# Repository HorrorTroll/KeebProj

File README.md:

# Keyboards

This repository is warehouse of my keyboard architecture.

## Paws60

### About Paws60

The Paws60 is 63 key (60%) keyboard. It is based on [Bakeneko60](https://github.com/kkatano/bakeneko-60). Thank you so much kkatano.😊

[Firmware](https://github.com/qmk/qmk_firmware/tree/master/keyboards/horrortroll/paws60)  
[Hardware data](https://github.com/HorrorTroll/Keeb_Project/tree/default/paws60)

## Sakura50

### About Sakura50

The Sakura50 is 56 keys (50%) keyboard.

[Firmware]()  
[Hardware data](https://github.com/HorrorTroll/Keeb_Project/tree/default/sakura50)

## Keeb65 (Abandon)

### About Keeb65

The Keeb65 is 67 key (65%) keyboard. For many reason, it become abandon project.

[Firmware]()  
[Hardware data](https://github.com/HorrorTroll/Keeb_Project/tree/default/keeb65)

## ToxicDog69

### About ToxicDog69

The ToxicDog69 is 69 keys Multi-layout (65%) keyboard.

[Firmware]()  
[Hardware data](https://github.com/HorrorTroll/Keeb_Project/tree/default/toxicdog69)

## LazuliPad

### About LazuliPad

The LazuliPad is a Numpad Multi-layout keyboard.

[Firmware]()  
[Hardware data](https://github.com/HorrorTroll/Keeb_Project/tree/default/lazulipad)

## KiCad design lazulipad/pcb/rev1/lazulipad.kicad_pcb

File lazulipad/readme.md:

# LazuliPad PCB
 A Numpad Multi-Layout Hotswap Type-C PCB, designed in KiCAD 6.99. The name was based on Lazuli Lapis stones.

**This board not have any prototyped yet!**

Renders (KiCAD):
- **Revision 1**:

## Features
**Revision 1**:
- Uses the AT32F403ACGT7 MCU (new), with 1MB of internal flash and 16MB of external flash
- Uses Kailh Hotswap Sockets
- Added anti-shearing to the hotswap sockets
- Holes of hotswap socket holes are plated, you can still solder in a switch, should a hotswap socket ever shear off for whatever reason
- Multi-layout (see below)
- USB-C connector
- Physical Reset and BOOT0 button for getting into bootloader if [bootmagic](https://github.com/qmk/qmk_firmware/blob/master/docs/feature_bootmagic.md) isn't available. Acessible both of them under PCB.
- SWD header for debugging
- ESD chip (PRTR5V0U2X) to prevent damage from electrostatic discharge
- Polyfuse to prevent overcurrent
- Stabilizer only supported Plate Mount, prevent 90-degree hotswap socket.
- Supported LCD module (ST7789 / 135 X 240).
- Supported 1 Rotary Encoder (EC11)
- Bonus: Curved traces and teardrops

## Firmware
**Coming soon!**

## Multi-Layout Support

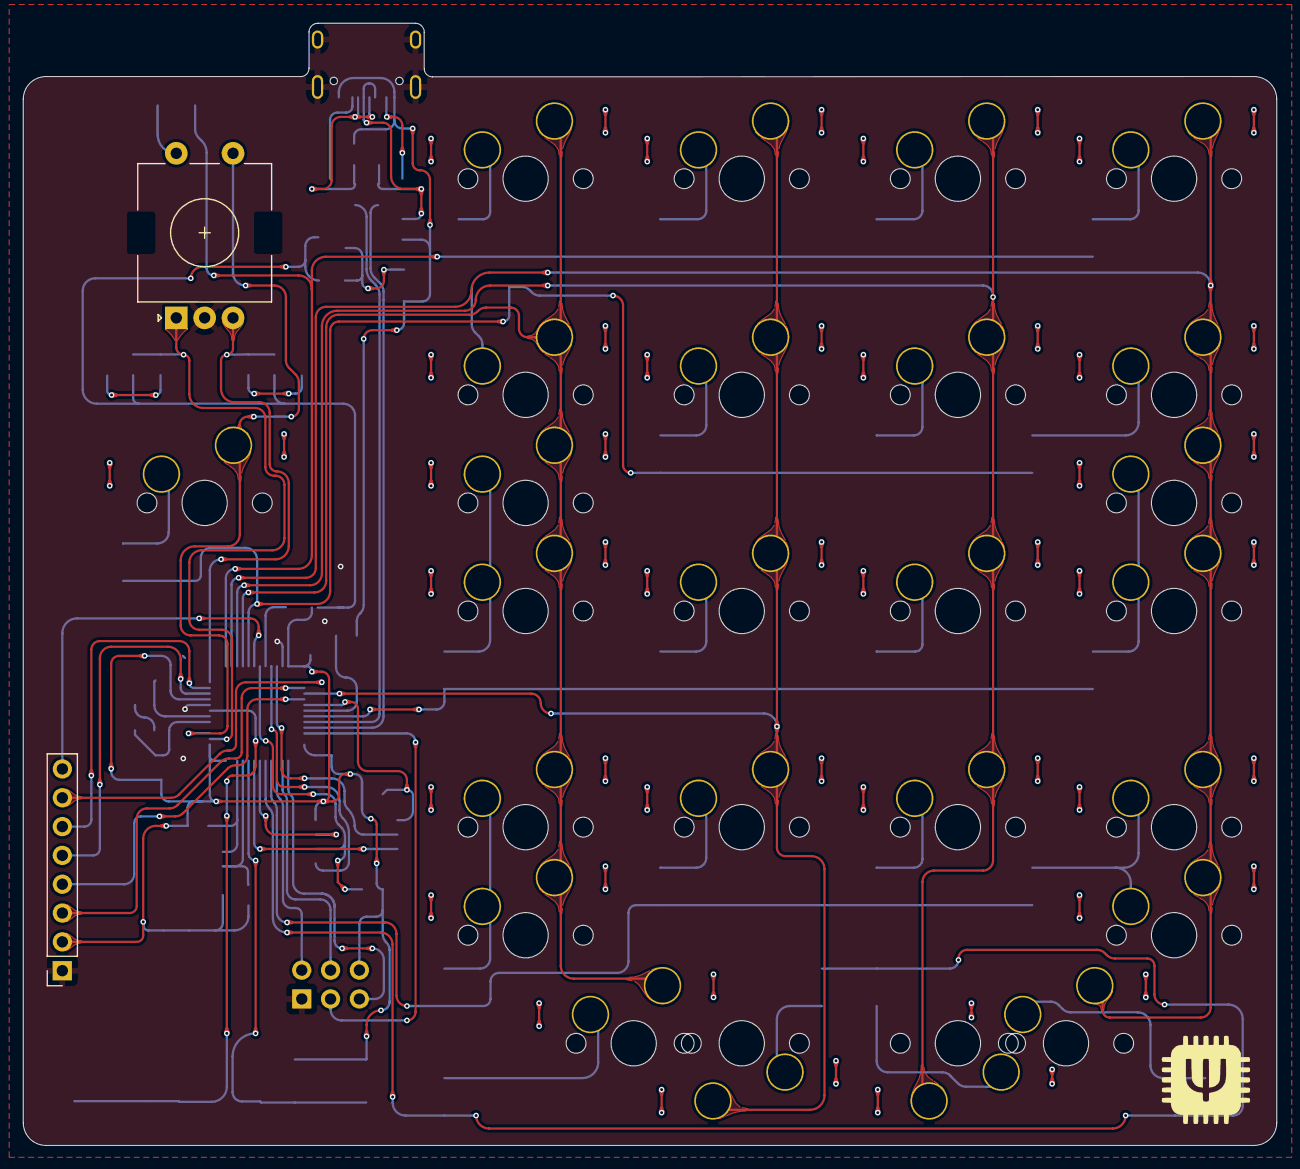
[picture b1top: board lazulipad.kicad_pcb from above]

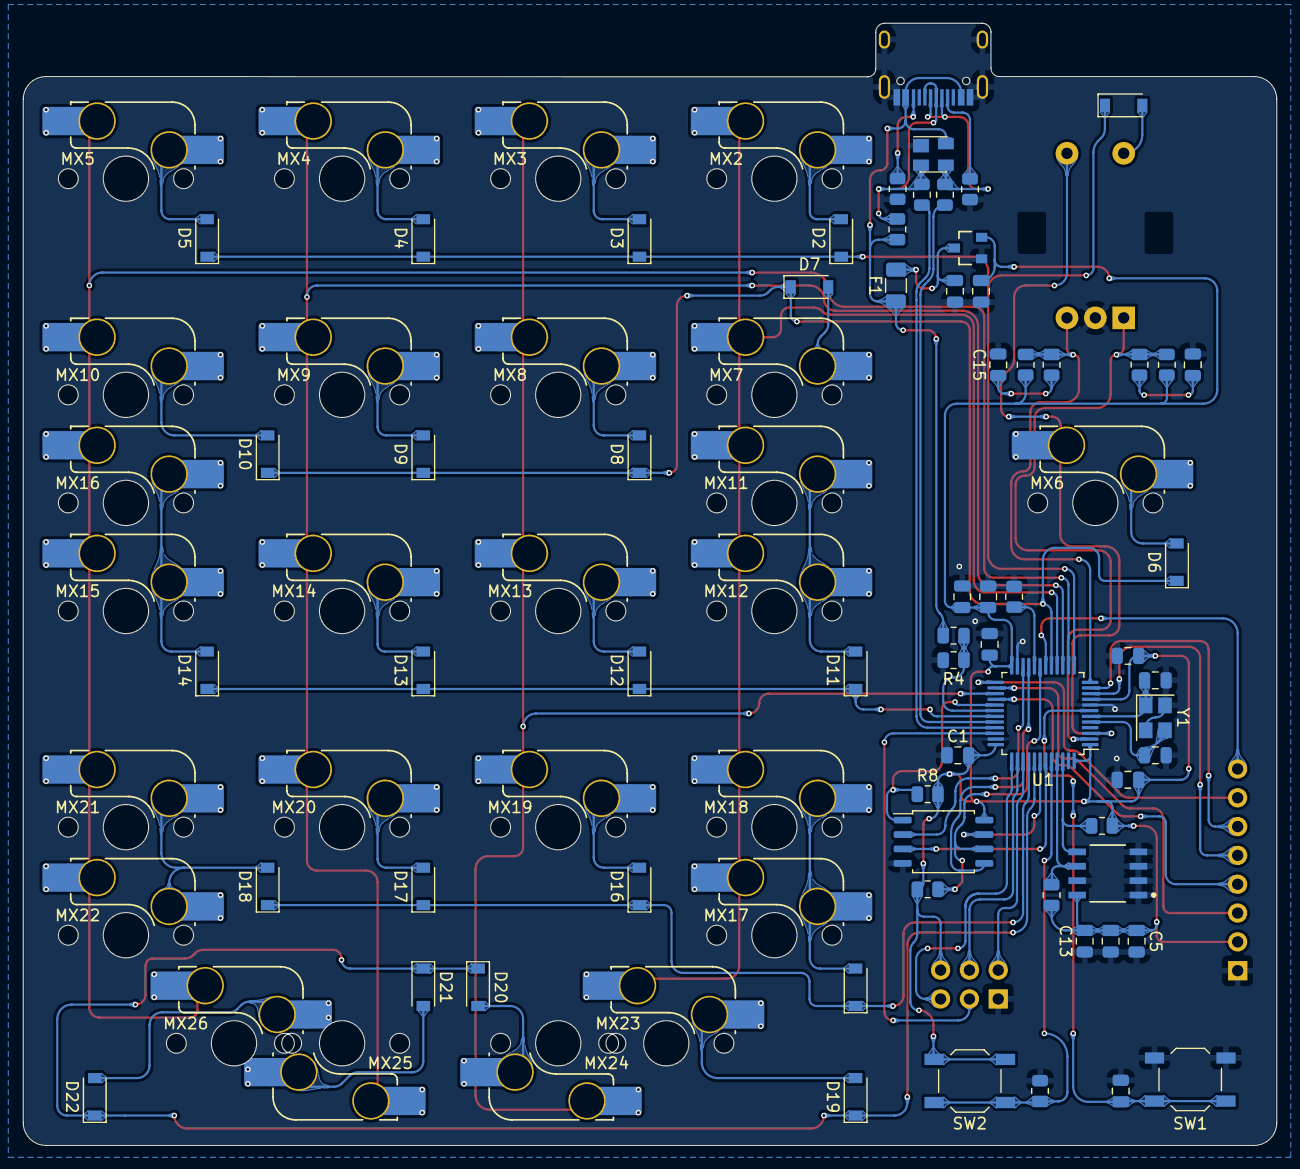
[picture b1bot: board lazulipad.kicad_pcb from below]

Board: 2 copper layers, 110.5 x 98.9 mm, 93 parts (90 on the bottom side), 70 nets.

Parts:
C1, C2, C5, C7, C13, C14, C15, C16: 100n; C_0805_2012Metric
C3: 10n; C_0805_2012Metric
C4, C11, C12: 1u; C_0805_2012Metric
C6, C8: 4.7u; C_0805_2012Metric
C9, C10: 22p; C_0805_2012Metric
D1, D2, D3, D4, D5, D6, D7, D8, D9, D10, D11, D12, D13, D14, D15, D16, D17, D18, D19, D20, D21, D22: 1N4148W; D_SOD-123
ESD1: PRTR5V0U2X; SOT-143
F1: 500mA; Fuse_1206_3216Metric
J1: ARM-JTAG-6; Reset_Pretty_nosilk
LCD1: LCD-ST7789-1.14in; PinSocket_1x08_P2.54mm_Vertical
MX1: Enc; RotaryEncoder_EC11
MX2, MX3, MX4, MX5, MX6, MX7, MX8, MX9, MX10, MX12, MX13, MX14, MX15, MX18, MX19, MX20, MX21, MX24, MX25: 1u; SW_MX_HS_1u
MX11, MX16, MX17, MX22: 2u; SW_MX_HS_2u_vertical
MX23, MX26: 2u; SW_MX_HS_2u
R1, R2, R5, R6, R8: 10K; R_0805_2012Metric
R3: 100k; R_0805_2012Metric
R4: 200k; R_0805_2012Metric
R7: 1K; R_0805_2012Metric
R9, R10: 5.1k; R_0805_2012Metric
R11, R12, R13, R14: 10k; R_0805_2012Metric
R15, R16: 22R; R_0805_2012Metric
R17: 1.5K; R_0805_2012Metric
RG1: XC6206P332MR; Torex-XC6206P332MR
SW1: RESET; SW_SPST_TL3342
SW2: BOOT0; SW_SPST_TL3342
U1: STM32F103CBTx; LQFP-48_7x7mm_P0.5mm
U2: W25Q128JVS; SOIC-8_5.23x5.23mm_P1.27mm
U3: AT24C512C-SSHD-T; Microchip-C04-057-SN-0-E-MFG
USB1: HRO-TYPE-C-31-M-12
Y1: 8Mhz; Crystal_SMD_3225-4Pin_3.2x2.5mm

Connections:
+3V3: C1.2, C2.2, C3.2, C4.2, C5.1, C6.1, C7.1, C8.1, C12.1, C13.2, J1.1 (VCC), LCD1.2, R5.2, R6.2, R7.2, R8.2, R11.1, R12.1, RG1.2 (VOUT), SW2.2, U1.1 (VBAT), U1.9 (VDDA), U1.24 (VDD), U1.36 (VDD), U1.48 (VDD), U2.8 (VCC), U3.8 (VCC)
+5V: C11.1, F1.2, RG1.3 (VIN)
/DM: ESD1.3 (I/O2), R16.2, USB1.5 (DN2), USB1.7 (DN1)
/DP: ESD1.2 (I/O1), R15.2, R17.2, USB1.6 (DP1), USB1.8 (DP2)
/VBUS_DETECT: R3.2, R4.1, U1.30 (PA9)
BLK: LCD1.8, U1.18 (PB0)
BOOT0: R1.1, SW2.1, U1.44 (BOOT0)
BOOT1: R2.1, U1.20 (PB2)
CS: LCD1.7, U1.25 (PB12)
Col0: MX1.S1, MX6.2 (B), U1.3 (PC14)
Col1: MX2.2 (B), MX7.2 (B), MX11.2 (B), MX12.2 (B), MX17.2 (B), MX18.2 (B), MX23.2 (B), U1.16 (PA6)
Col2: MX3.2 (B), MX8.2 (B), MX13.2 (B), MX19.2 (B), MX24.2 (B), U1.27 (PB14)
Col3: MX4.2 (B), MX9.2 (B), MX14.2 (B), MX20.2 (B), MX25.2 (B), U1.15 (PA5)
Col4: MX5.2 (B), MX10.2 (B), MX15.2 (B), MX16.2 (B), MX21.2 (B), MX22.2 (B), MX26.2 (B), U1.14 (PA4)
D+: R15.1, U1.33 (PA12)
D-: R16.1, U1.32 (PA11)
DC: LCD1.6, U1.11 (PA1)
GND: C1.1, C2.1, C3.1, C4.1, C5.2, C6.2, C7.2, C8.2, C9.2, C10.2, C11.2, C12.2, C13.1, C14.2, C15.2, C16.1, ESD1.1 (GND), J1.6 (GND), LCD1.1, MX1.C, R1.2, R2.2, R4.2, R9.1, R10.2, RG1.1 (VSS), SW1.1, U1.8 (VSSA), U1.23 (VSS), U1.35 (VSS), U1.47 (VSS), U2.4 (GND), U3.1 (A0), U3.2 (A1), U3.3 (A2), U3.4 (GND), U3.7 (WP), USB1.1 (GND), USB1.12 (GND), USB1.13 (SHIELD), Y1.2, Y1.4
JTDI: J1.3 (JTDI), U1.38 (PA15)
JTDO: J1.5 (JTDO), U1.39 (PB3)
MOSI: LCD1.4, U1.28 (PB15)
NRST: C16.2, SW1.2, U1.7 (NRST)
unnamed: C14.1, R13.2
unnamed: C15.1, R14.2
unnamed: D1.2 (A), MX1.S2
unnamed: D2.2 (A), MX2.1 (A)
unnamed: D3.2 (A), MX3.1 (A)
unnamed: D4.2 (A), MX4.1 (A)
unnamed: D5.2 (A), MX5.1 (A)
unnamed: D6.2 (A), MX6.1 (A)
unnamed: D7.2 (A), MX7.1 (A)
unnamed: D8.2 (A), MX8.1 (A)
unnamed: D9.2 (A), MX9.1 (A)
unnamed: D10.2 (A), MX10.1 (A)
unnamed: D11.2 (A), MX11.1 (A), MX12.1 (A)
unnamed: D12.2 (A), MX13.1 (A)
unnamed: D13.2 (A), MX14.1 (A)
unnamed: D14.2 (A), MX15.1 (A), MX16.1 (A)
unnamed: D15.2 (A), MX17.1 (A), MX18.1 (A)
unnamed: D16.2 (A), MX19.1 (A)
unnamed: D17.2 (A), MX20.1 (A)
unnamed: D18.2 (A), MX21.1 (A), MX22.1 (A)
unnamed: D19.2 (A), MX23.1 (A)
unnamed: D20.2 (A), MX24.1 (A)
unnamed: D21.2 (A), MX25.1 (A)
unnamed: D22.2 (A), MX26.1 (A)
unnamed: R9.2, USB1.4 (CC1)
unnamed: R10.1, USB1.10 (CC2)
RESET: LCD1.5, U1.10 (PA0)
ROT0: MX1.A, R11.2, R13.1, U1.2 (PC13)
ROT1: MX1.B, R12.2, R14.1, U1.12 (PA2)
Row0: D1.1 (K), D2.1 (K), D3.1 (K), D4.1 (K), D5.1 (K), U1.13 (PA3)
Row1: D6.1 (K), D7.1 (K), D8.1 (K), D9.1 (K), D10.1 (K), U1.17 (PA7)
Row2: D11.1 (K), D12.1 (K), D13.1 (K), D14.1 (K), U1.31 (PA10)
Row3: D15.1 (K), D16.1 (K), D17.1 (K), D18.1 (K), U1.40 (PB4)
Row4: D19.1 (K), D20.1 (K), D21.1 (K), D22.1 (K), U1.41 (PB5)
SCK: LCD1.3, U1.26 (PB13)
SCL: R6.1, U1.45 (PB8), U3.6 (SCL)
SDA: R5.1, U1.46 (PB9), U3.5 (SDA)
SPIM_CS: R8.1, U1.29 (PA8), U2.1 (~CS)
SPIM_IO0: U1.21 (PB10), U2.5 (DI(IO0))
SPIM_IO1: U1.22 (PB11), U2.2 (DO(IO1))
SPIM_IO2: U1.43 (PB7), U2.3 (IO2)
SPIM_IO3: U1.42 (PB6), U2.7 (IO3)
SPIM_SCK: R7.1, U1.19 (PB1), U2.6 (CLK)
SWCLK-JTCK: J1.2 (SWCLK), U1.37 (PA14)
SWDIO-JTMS: J1.4 (SWDIO), U1.34 (PA13)
VBUS: ESD1.4 (VCC), F1.1, R3.1, R17.1, USB1.2 (VBUS), USB1.11 (VBUS)
XTAL1: C9.1, U1.5 (PD0), Y1.3
XTAL2: C10.1, U1.6 (PD1), Y1.1

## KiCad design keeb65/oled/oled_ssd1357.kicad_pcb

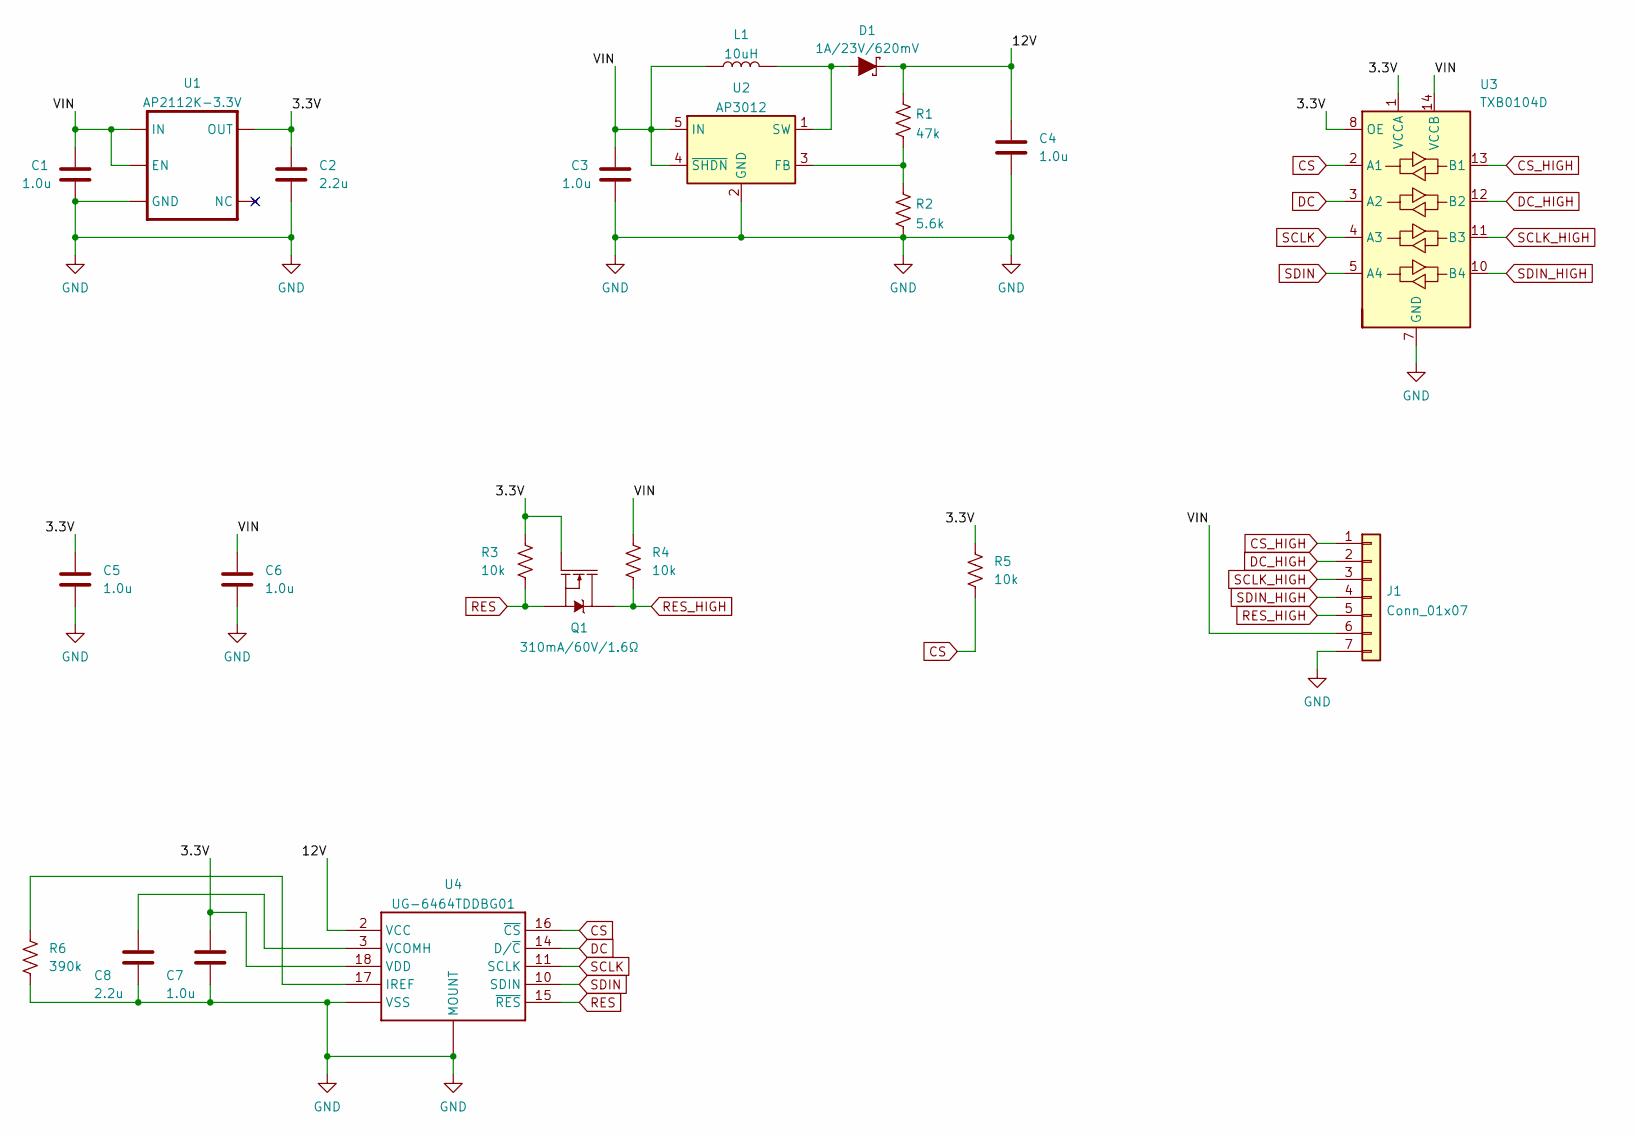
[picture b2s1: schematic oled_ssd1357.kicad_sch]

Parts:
C1, C3, C4, C5, C6, C7: 1.0u; C_0603_1608Metric
C2, C8: 2.2u; C_0603_1608Metric
D1: 1A/23V/620mV; SOD-323
J1: Conn_01x07; Molex_200528-0070_1x07-1MP_P1.00mm_Horizontal
L1: 10uH; CDRH124
Q1: 310mA/60V/1.6Ω; SOT65P210X110-3N
R1: 47k; R_0603_1608Metric
R2: 5.6k; R_0603_1608Metric
R3, R4, R5: 10k; R_0603_1608Metric
R6: 390k; R_0603_1608Metric
U1: AP2112K-3.3V; SOT-23-5
U2: AP3012; SOT-23-5
U3: TXB0104D; TXB0104
U4: UG-6464TDDBG01; AMPHENOL_10051922-2010ELF

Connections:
/3.3V: C2.1, C5.1, C7.1, Q1.1 (G), R3.1, R5.1, U1.5 (OUT), U3.1 (VCCA), U3.8 (OE), U4.18 (VDD)
/12V: C4.1, D1.C, R1.1, U4.2 (VCC)
/VIN: C1.1, C3.1, C6.1, J1.6, L1.P$1 (1), R4.1, U1.1 (IN), U1.3 (EN), U2.4 (~SHDN), U2.5 (IN), U3.14 (VCCB)
CS: R5.2, U3.2 (A1), U4.16 (~CS)
CS_HIGH: J1.1, U3.13 (B1)
DC: U3.3 (A2), U4.14 (D/~C)
DC_HIGH: J1.2, U3.12 (B2)
GND: C1.2, C2.2, C3.2, C4.2, C5.2, C6.2, C7.2, C8.2, J1.7, R2.2, R6.2, U1.2 (GND), U2.2 (GND), U3.7 (GND), U4.1 (VSS), U4.19 (VSS), U4.20 (VSS), U4.P$21 (MOUNT), U4.P$22 (MOUNT)
unnamed: C8.1, U4.3 (VCOMH)
unnamed: D1.A, L1.P$2 (2), U2.1 (SW)
unnamed: R1.2, R2.1, U2.3 (FB)
unnamed: R6.1, U4.17 (IREF)
RES: Q1.2 (S), R3.2, U4.15 (~RES)
RES_HIGH: J1.5, Q1.3 (D), R4.2
SCLK: U3.4 (A3), U4.11 (SCLK)
SCLK_HIGH: J1.3, U3.11 (B3)
SDIN: U3.5 (A4), U4.10 (SDIN)
SDIN_HIGH: J1.4, U3.10 (B4)

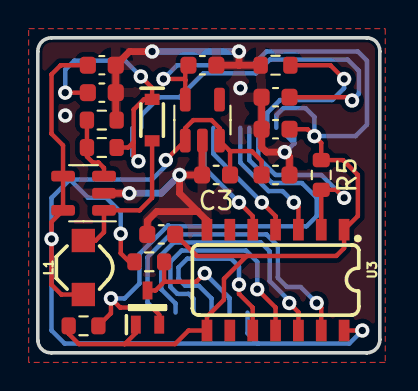
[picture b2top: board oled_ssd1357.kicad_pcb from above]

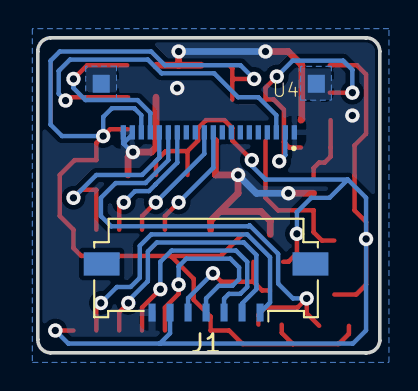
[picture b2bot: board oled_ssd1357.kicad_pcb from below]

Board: 2 copper layers, 19.0 x 17.5 mm, 22 parts (2 on the bottom side), 18 nets.

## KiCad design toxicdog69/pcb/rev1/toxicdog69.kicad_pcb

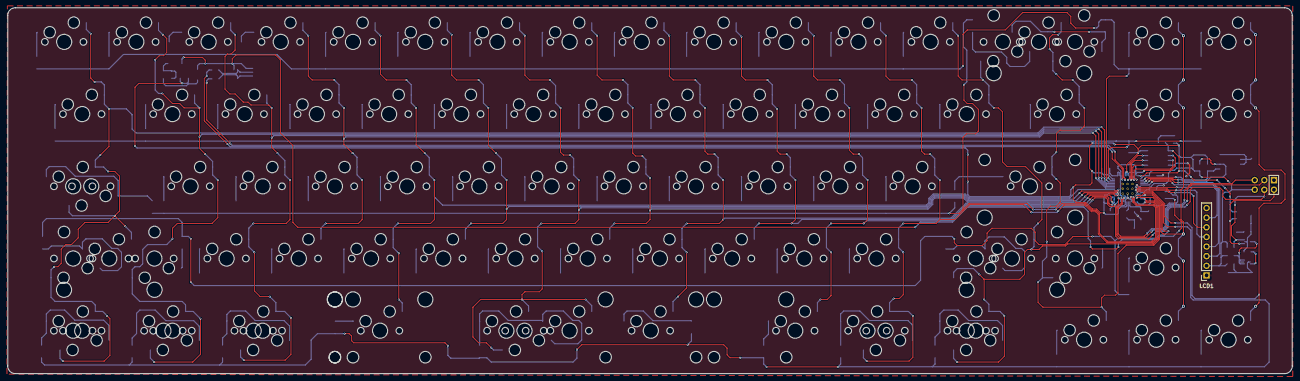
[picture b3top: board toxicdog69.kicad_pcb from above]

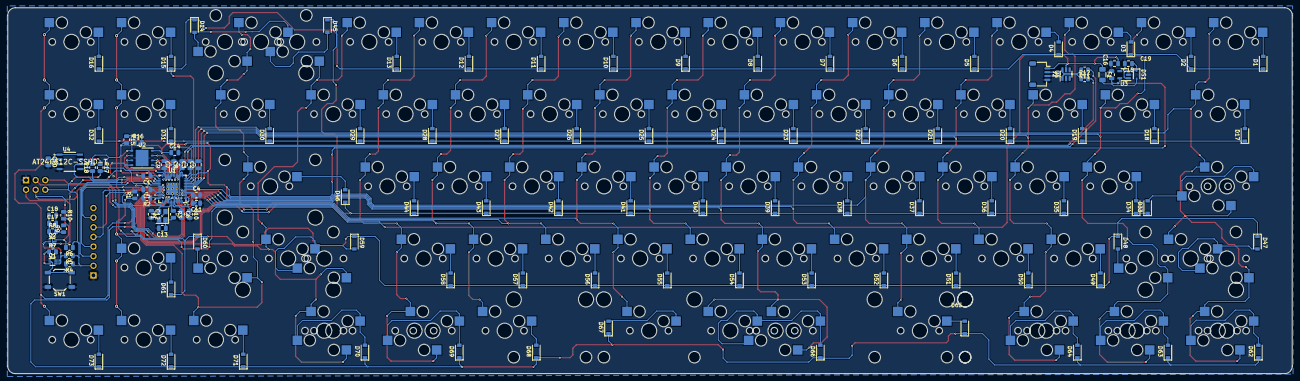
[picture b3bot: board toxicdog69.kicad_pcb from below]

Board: 2 copper layers, 338.9 x 96.5 mm, 207 parts (121 on the bottom side), 132 nets.

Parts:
C1, C2, C3, C4, C5, C6, C7, C8, C9, C14, C20: 100n; C_0805_2012Metric
C10, C11: 1u; C_0805_2012Metric
C12, C13: 15p; C_0805_2012Metric
C15, C16, C17, C18, C19: 4u7; C_0805_2012Metric
D1, D2, D3, D4, D5, D6, D7, D8, D9, D10, D11, D12, D13, D14, D15, D16, D17, D18, D19, D20, D21, D22, D23, D24, D25, D26, D27, D28, D29, D30, D31, D32, D33, D34, D35, D36, D37, D38, D39, D40, D41, D42, D43, D44, D45, D46, D47, D48, D49, D50, D51, D52, D53, D54, D55, D56, D57, D58, D59, D60, D61, D62, D63, D64, D65, D66, D67, D68, D69, D70, D71, D72, D73: 1N4148W; D_SOD-123
DS1: B5817WS; D_SOD-323
F1: 500mA; Fuse_1206_3216Metric
J1: RP2040-JTAG-6; Reset_Pretty
J2: USB Daughterboard; JST_SH_SM04B-SRSS-TB_1x04-1MP_P1.00mm_Horizontal
LCD1: LCD-ST7735-0.96in; PinSocket_1x08_P2.54mm_Vertical
MX1, MX2, MX3, MX4, MX5, MX6, MX7, MX8, MX9, MX10, MX11, MX12, MX13, MX14, MX16, MX17, MX19, MX20, MX21, MX22, MX23, MX24, MX25, MX26, MX27, MX28, MX29, MX30, MX32, MX33, MX36, MX37, MX38, MX39, MX40, MX41, MX42, MX43, MX44, MX45, MX46, MX47, MX51, MX52, MX53, MX54, MX55, MX56, MX57, MX58, MX59, MX60, MX61, MX64, MX65, MX75, MX76, MX77, MX79: 1u; MXOnly-1U-Hotswap
MX15: 2u; MXOnly-2U-Hotswap
MX18, MX31, MX78, MX80, MX83: 1.5u; MXOnly-1.5U-Hotswap
MX34, MX49, MX66, MX67, MX68, MX70, MX72, MX73, MX74, MX82: 1.25u; MXOnly-1.25U-Hotswap
MX35, MX62: 1.75u; MXOnly-1.75U-Hotswap
MX48, MX50: 2.25u; MXOnly-2.25U-Hotswap
MX63: 2.75u; MXOnly-2.75U-Hotswap
MX69: 2.25u; MXOnly-2.25U-Hotswap-ReversedStabilizers
MX71: 2.75u; MXOnly-2.75U-Hotswap-ReversedStabilizers
MX81: 7u; MXOnly-7U-Hotswap-ReversedStabilizers
MX84: 6.25u; MXOnly-6.25U-Hotswap
Q1, Q2: 2N7002VC-7; SOT-563
R1: 2K2; R_0805_2012Metric
R2, R4, R5, R6, R15, R16: 5K1; R_0805_2012Metric
R3, R10: 1K; R_0805_2012Metric
R7, R8, R9: 51K; R_0805_2012Metric
R11, R12: 27R; R_0805_2012Metric
R17, R18: 10K; R_0805_2012Metric
SW1: SWITCH; SW_SPST_TL3342
U1: RP2040; RP2040-QFN-56
U2: GD25Q128EWIGR; WSON-8-1EP_6x5mm_P1.27mm_EP3.4x4.3mm
U3: AP7365-33WG-7; SOT-23-5
U4: AT24C512C-SSHD-T; Microchip-C04-057-SN-0-E-MFG
U5: SRV05-4; SOT-23-6
Y1: 12Mhz; Crystal_SMD_3225-4Pin_3.2x2.5mm

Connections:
+1V1: C8.1, C9.1, C10.1, U1.23 (DVDD), U1.45 (VREG_VOUT), U1.50 (DVDD)
+3V3: C1.1, C2.1, C3.1, C4.1, C5.1, C6.1, C7.1, C11.2, C14.1, C16.1, J1.1 (VCC), LCD1.2, R4.1, R5.1, R6.1, R15.2, R17.2, R18.2, U1.1 (IOVDD), U1.10 (IOVDD), U1.22 (IOVDD), U1.33 (IOVDD), U1.42 (IOVDD), U1.43 (ADC_AVDD), U1.44 (VREG_VIN), U1.48 (USB_VDD), U1.49 (IOVDD), U2.8 (VCC), U3.5 (VOUT)
+5V: C15.1, DS1.1 (K), U3.1 (VIN), U3.3 (EN)
/DM: J2.2, R11.2, U5.6 (IO4)
/DP: J2.3, R12.1, U5.1 (IO1)
/SWITCH: Q1.2 (G), R4.2, SW1.2
/VBUS_DETECT: R1.2, R2.1, U1.16 (GPIO13)
/nRST: J1.3 (nRST), Q2.6 (D), R6.2, U1.26 (~RUN)
BOOT: J1.5 (BOOT), Q2.4 (S), R10.2
CS: LCD1.7, U1.6 (GPIO4)
Col0: MX1.2 (B), MX18.2 (B), MX34.2 (B), MX35.2 (B), MX49.2 (B), MX50.2 (B), MX66.2 (B), MX78.2 (B), U1.39 (GPIO27/ADC1)
Col1: MX2.2 (B), MX19.2 (B), MX36.2 (B), MX51.2 (B), MX67.2 (B), MX79.2 (B), U1.38 (GPIO26/ADC0)
Col2: MX3.2 (B), MX20.2 (B), MX37.2 (B), MX52.2 (B), MX68.2 (B), MX80.2 (B), U1.37 (GPIO25)
Col3: MX4.2 (B), MX21.2 (B), MX38.2 (B), MX53.2 (B), U1.36 (GPIO24)
Col4: MX5.2 (B), MX22.2 (B), MX39.2 (B), MX54.2 (B), MX69.2 (B), U1.35 (GPIO23)
Col5: MX6.2 (B), MX23.2 (B), MX40.2 (B), MX55.2 (B), U1.34 (GPIO22)
Col6: MX7.2 (B), MX24.2 (B), MX41.2 (B), MX56.2 (B), MX70.2 (B), MX81.2 (B), MX84.2 (B), U1.32 (GPIO21)
Col7: MX8.2 (B), MX25.2 (B), MX42.2 (B), MX57.2 (B), U1.31 (GPIO20)
Col8: MX9.2 (B), MX26.2 (B), MX43.2 (B), MX58.2 (B), MX71.2 (B), U1.30 (GPIO19)
Col9: MX10.2 (B), MX27.2 (B), MX44.2 (B), MX59.2 (B), U1.29 (GPIO18)
Col10: MX11.2 (B), MX28.2 (B), MX45.2 (B), MX60.2 (B), MX72.2 (B), U1.28 (GPIO17)
Col11: MX12.2 (B), MX29.2 (B), MX46.2 (B), MX61.2 (B), MX73.2 (B), MX82.2 (B), U1.17 (GPIO14)
Col12: MX13.2 (B), MX30.2 (B), MX47.2 (B), MX62.2 (B), MX63.2 (B), MX74.2 (B), MX83.2 (B), U1.15 (GPIO12)
Col13: MX14.2 (B), MX15.2 (B), MX31.2 (B), MX48.2 (B), MX64.2 (B), MX75.2 (B), U1.14 (GPIO11)
Col14: MX16.2 (B), MX32.2 (B), MX65.2 (B), MX76.2 (B), U1.13 (GPIO10)
Col15: MX17.2 (B), MX33.2 (B), MX77.2 (B), U1.9 (GPIO7)
D+: R12.2, U1.47 (D+)
D-: R11.1, U1.46 (D-)
DC: LCD1.6, U1.8 (GPIO6)
FLASH_SCK: U1.52 (QSPI_SCLK), U2.6 (CLK)
FLASH_SD0: U1.53 (QSPI_SD0), U2.5 (DI(IO0))
FLASH_SD1: U1.55 (QSPI_SD1), U2.2 (DO(IO1))
FLASH_SD2: U1.54 (QSPI_SD2), U2.3 (IO2)
FLASH_SD3: U1.51 (QSPI_SD3), U2.7 (IO3)
FLASH_nCS: R10.1, R16.1, U1.56 (QSPI_SS_N), U2.1 (~CS)
GND: C1.2, C2.2, C3.2, C4.2, C5.2, C6.2, C7.2, C8.2, C9.2, C10.2, C11.1, C12.2, C13.2, C14.2, C15.2, C16.2, C17.2, C18.2, C19.1, C20.2, J1.6 (GND), J2.4, LCD1.1, Q1.1 (S), Q2.1 (S), Q2.3 (D), R2.2, R9.2, SW1.1, U1.19 (TESTEN), U1.57 (GND), U2.4 (GND), U2.9 (GND), U3.2 (GND), U4.4 (GND), U4.7 (WP), U5.2 (VN), Y1.2, Y1.4
MOSI: LCD1.4, U1.5 (GPIO3)
unnamed: C13.1, R3.2, Y1.1
unnamed: D1.2 (A), MX1.1 (A)
unnamed: D2.2 (A), MX2.1 (A)
unnamed: D3.2 (A), MX3.1 (A)
unnamed: D4.2 (A), MX4.1 (A)
unnamed: D5.2 (A), MX5.1 (A)
unnamed: D6.2 (A), MX6.1 (A)
unnamed: D7.2 (A), MX7.1 (A)
unnamed: D8.2 (A), MX8.1 (A)
unnamed: D9.2 (A), MX9.1 (A)
unnamed: D10.2 (A), MX10.1 (A)
unnamed: D11.2 (A), MX11.1 (A)
unnamed: D12.2 (A), MX12.1 (A)
unnamed: D13.2 (A), MX13.1 (A)
unnamed: D14.2 (A), MX14.1 (A), MX15.1 (A)
unnamed: D15.2 (A), MX16.1 (A)
unnamed: D16.2 (A), MX17.1 (A)
unnamed: D17.2 (A), MX18.1 (A)
unnamed: D18.2 (A), MX19.1 (A)
unnamed: D19.2 (A), MX20.1 (A)
unnamed: D20.2 (A), MX21.1 (A)
unnamed: D21.2 (A), MX22.1 (A)
unnamed: D22.2 (A), MX23.1 (A)
unnamed: D23.2 (A), MX24.1 (A)
unnamed: D24.2 (A), MX25.1 (A)
unnamed: D25.2 (A), MX26.1 (A)
unnamed: D26.2 (A), MX27.1 (A)
unnamed: D27.2 (A), MX28.1 (A)
unnamed: D28.2 (A), MX29.1 (A)
unnamed: D29.2 (A), MX30.1 (A)
unnamed: D30.2 (A), MX31.1 (A)
unnamed: D31.2 (A), MX32.1 (A)
unnamed: D32.2 (A), MX33.1 (A)
unnamed: D33.2 (A), MX34.1 (A), MX35.1 (A)
unnamed: D34.2 (A), MX36.1 (A)
unnamed: D35.2 (A), MX37.1 (A)
unnamed: D36.2 (A), MX38.1 (A)
unnamed: D37.2 (A), MX39.1 (A)
unnamed: D38.2 (A), MX40.1 (A)
unnamed: D39.2 (A), MX41.1 (A)
unnamed: D40.2 (A), MX42.1 (A)
unnamed: D41.2 (A), MX43.1 (A)
unnamed: D42.2 (A), MX44.1 (A)
unnamed: D43.2 (A), MX45.1 (A)
unnamed: D44.2 (A), MX46.1 (A)
unnamed: D45.2 (A), MX47.1 (A)
unnamed: D46.2 (A), MX48.1 (A)
unnamed: D47.2 (A), MX49.1 (A), MX50.1 (A)
unnamed: D48.2 (A), MX51.1 (A)
unnamed: D49.2 (A), MX52.1 (A)
unnamed: D50.2 (A), MX53.1 (A)
unnamed: D51.2 (A), MX54.1 (A)
unnamed: D52.2 (A), MX55.1 (A)
unnamed: D53.2 (A), MX56.1 (A)
unnamed: D54.2 (A), MX57.1 (A)
unnamed: D55.2 (A), MX58.1 (A)
unnamed: D56.2 (A), MX59.1 (A)
unnamed: D57.2 (A), MX60.1 (A)
unnamed: D58.2 (A), MX61.1 (A)
unnamed: D59.2 (A), MX62.1 (A), MX63.1 (A)
unnamed: D60.2 (A), MX64.1 (A)
unnamed: D61.2 (A), MX65.1 (A)
unnamed: D62.2 (A), MX66.1 (A), MX78.1 (A)
unnamed: D63.2 (A), MX67.1 (A), MX79.1 (A)
unnamed: D64.2 (A), MX68.1 (A), MX80.1 (A)
unnamed: D65.2 (A), MX69.1 (A)
unnamed: D66.2 (A), MX70.1 (A), MX81.1 (A), MX84.1 (A)
unnamed: D67.2 (A), MX71.1 (A)
unnamed: D68.2 (A), MX72.1 (A)
unnamed: D69.2 (A), MX73.1 (A), MX82.1 (A)
unnamed: D70.2 (A), MX74.1 (A), MX83.1 (A)
unnamed: D71.2 (A), MX75.1 (A)
unnamed: D72.2 (A), MX76.1 (A)
unnamed: D73.2 (A), MX77.1 (A)
unnamed: DS1.2 (A), F1.2
unnamed: Q1.3 (D), R7.1
unnamed: Q1.4 (S), Q1.5 (G), Q1.6 (D), Q2.2 (G), R5.2
unnamed: C17.1, C18.1, Q2.5 (G), R7.2, R8.1
unnamed: R8.2, R9.1
unnamed: R15.1, R16.2
unnamed: C20.1, U4.1 (A0), U4.2 (A1), U4.3 (A2), U4.8 (VCC)
RESET: LCD1.5, U1.7 (GPIO5)
Row0: D1.1 (K), D2.1 (K), D3.1 (K), D4.1 (K), D5.1 (K), D6.1 (K), D7.1 (K), D8.1 (K), D9.1 (K), D10.1 (K), D11.1 (K), D12.1 (K), D13.1 (K), D14.1 (K), D15.1 (K), D16.1 (K), U1.40 (GPIO28/ADC2)
Row1: D17.1 (K), D18.1 (K), D19.1 (K), D20.1 (K), D21.1 (K), D22.1 (K), D23.1 (K), D24.1 (K), D25.1 (K), D26.1 (K), D27.1 (K), D28.1 (K), D29.1 (K), D30.1 (K), D31.1 (K), D32.1 (K), U1.41 (GPIO29/ADC3)
Row2: D33.1 (K), D34.1 (K), D35.1 (K), D36.1 (K), D37.1 (K), D38.1 (K), D39.1 (K), D40.1 (K), D41.1 (K), D42.1 (K), D43.1 (K), D44.1 (K), D45.1 (K), D46.1 (K), U1.18 (GPIO15)
Row3: D47.1 (K), D48.1 (K), D49.1 (K), D50.1 (K), D51.1 (K), D52.1 (K), D53.1 (K), D54.1 (K), D55.1 (K), D56.1 (K), D57.1 (K), D58.1 (K), D59.1 (K), D60.1 (K), D61.1 (K), U1.12 (GPIO9)
Row4: D62.1 (K), D63.1 (K), D64.1 (K), D65.1 (K), D66.1 (K), D67.1 (K), D68.1 (K), D69.1 (K), D70.1 (K), D71.1 (K), D72.1 (K), D73.1 (K), U1.11 (GPIO8)
SCK: LCD1.3, U1.4 (GPIO2)
SCL: R17.1, U1.3 (GPIO1), U4.6 (SCL)
SDA: R18.1, U1.2 (GPIO0), U4.5 (SDA)
SWCLK: J1.2 (SWCLK), U1.24 (SWCLK)
SWDIO: J1.4 (SWDIO), U1.25 (SWDIO)
VBUS: C19.2, F1.1, J2.1, R1.1, U5.5 (VP)
XTAL1: C12.1, U1.20 (XTAL_IN), Y1.3
XTAL2: R3.1, U1.21 (XTAL_OUT)

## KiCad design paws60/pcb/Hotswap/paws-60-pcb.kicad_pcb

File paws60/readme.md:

# Paws60 PCB
 A 60% Multi-Layout Hotswap PCB, designed in KiCAD 6.99. The name was based on Cat and Dog paws.

**This board not have prototyped for Rev 2 yet! Only Rev 1 was been printed and used.**

Renders (KiCAD):
- **Revision 1**:

- **Revision 2**:

IRL images:
- **Revision 1**:

- **Revision 2**:
**Coming soon!**

## Features
**Revision 1**:
- Uses the ATMEGA32U4-AU MCU, with 32KB of internal flash and 1KB of EEPROM
- Uses Kailh Hotswap Sockets
- Multi-layout (see below)
- JST connector for Unified Daughterboard support
- Physical BOOT button for getting into bootloader if [bootmagic](https://github.com/qmk/qmk_firmware/blob/master/docs/feature_bootmagic.md) isn't available. Acessible under PCB.
- SWD header for debugging
- ESD chip (SRV05-4) to prevent damage from electrostatic discharge
- Polyfuse to prevent overcurrent
- Bonus: Curved traces and teardrops

**Revision 2**:
- Uses the RP2040 MCU (new), with 16MB of external flash
- Uses Kailh Hotswap Sockets
- Added anti-shearing to the hotswap sockets
- Holes of hotswap socket holes are plated, you can still solder in a switch, should a hotswap socket ever shear off for whatever reason
- Multi-layout (see below)
- JST connector for Unified Daughterboard support
- Physical BOOT button for getting into bootloader if [bootmagic](https://github.com/qmk/qmk_firmware/blob/master/docs/feature_bootmagic.md) isn't available. Acessible under PCB.
- SWD header for debugging
- ESD chip (SRV05-4) to prevent damage from electrostatic discharge
- Polyfuse to prevent overcurrent
- 2 SK6812 Mini-E LED for Capslock and Esc
- Bonus: Curved traces and teardrops

## Firmware
- **Revision 1**:  
[QMK Firmware](https://github.com/qmk/qmk_firmware/tree/master/keyboards/horrortroll/paws60)  
[QMK Configurator](https://config.qmk.fm/#/horrortroll/paws60/LAYOUT_60_ansi_split_bs_rshift)

- **Revision 2**:
**Coming soon!**

## Multi-Layout Support
- **Revision 1**:

- **Revision 2**:

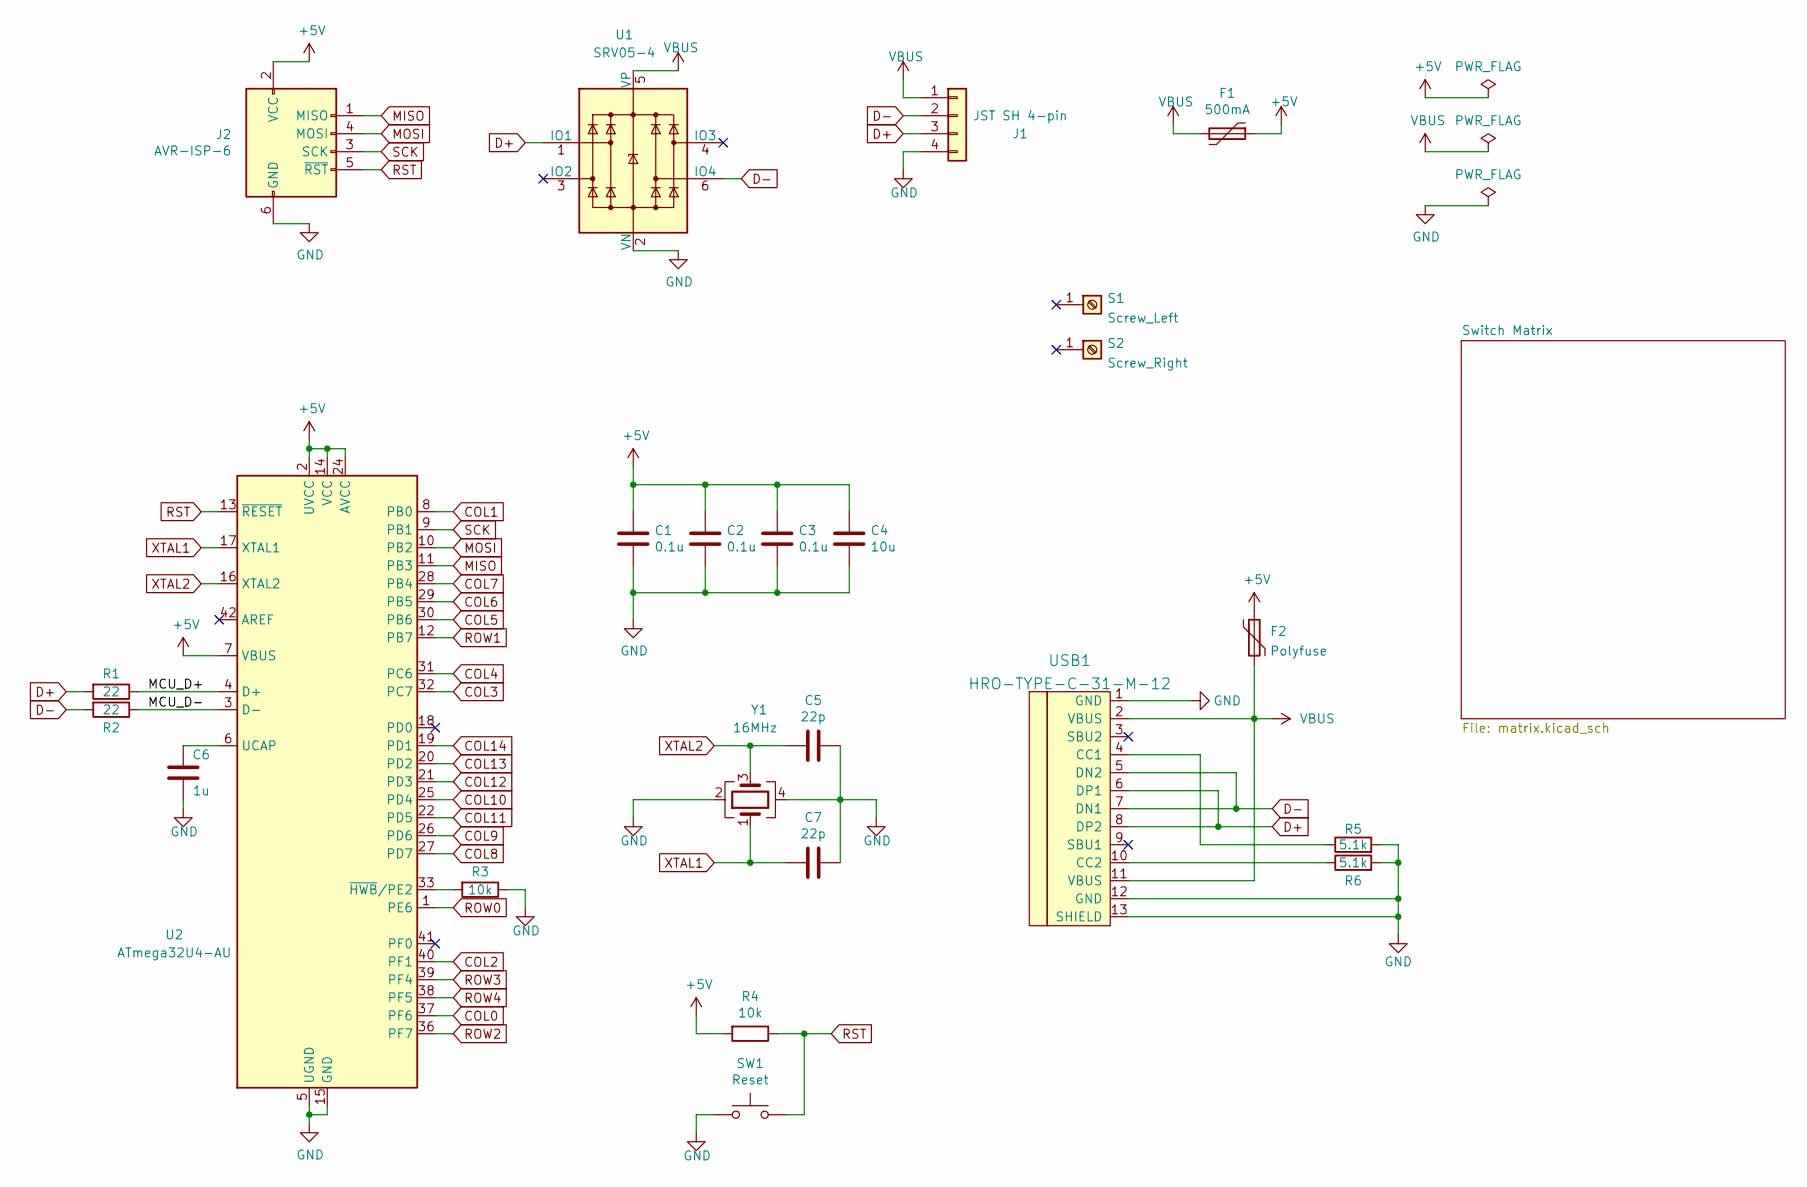
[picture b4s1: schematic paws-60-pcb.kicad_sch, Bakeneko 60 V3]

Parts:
C1, C2, C3: 0.1u; C_0805_2012Metric; LCSC Part # C49678
C4: 10u; C_0805_2012Metric; LCSC Part # C15850
C5, C7: 22p; C_0805_2012Metric; LCSC Part # C1804
C6: 1u; C_0805_2012Metric; LCSC Part # C28323
F1: 500mA; Fuse_1206_3216Metric; LCSC Part # C70076
F2: Polyfuse; R_0805_2012Metric
J1: JST SH 4-pin; JST_SH_SM04B-SRSS-TB_1x04-1MP_P1.00mm_Horizontal; LCSC Part # C160404
J2: AVR-ISP-6; Reset_Pretty
R1, R2: 22; R_0805_2012Metric; LCSC Part # C17561
R3, R4: 10k; R_0805_2012Metric; LCSC Part # C17414
R5, R6: 5.1k; R_0805_2012Metric
S1: Screw_Left; 10x5_7x2.5mm
S2: Screw_Right; 10x5_7x2.5mm
SW1: Reset; SW_SPST_TL3342; LCSC Part # C318884
U1: SRV05-4; SOT-23-6; LCSC Part # C85364
U2: ATmega32U4-AU; TQFP-44_10x10mm_P0.8mm; LCSC Part # C44854
USB1: HRO-TYPE-C-31-M-12
Y1: 16MHz; Crystal_SMD_3225-4Pin_3.2x2.5mm; LCSC Part # C13738

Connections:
+5V: C1.1, C2.1, C3.1, C4.1, F1.1, F2.1, J2.2 (VCC), R4.2, U2.2 (UVCC), U2.7 (VBUS), U2.14 (VCC), U2.24 (AVCC), U2.34 (VCC), U2.44 (AVCC)
/MCU_D+: R1.1, U2.4 (D+)
/MCU_D-: R2.1, U2.3 (D-)
COL0: U2.37 (PF6); also elsewhere on the board
COL1: U2.8 (PB0); also elsewhere on the board
COL2: U2.40 (PF1); also elsewhere on the board
COL3: U2.32 (PC7); also elsewhere on the board
COL4: U2.31 (PC6); also elsewhere on the board
COL5: U2.30 (PB6); also elsewhere on the board
COL6: U2.29 (PB5); also elsewhere on the board
COL7: U2.28 (PB4); also elsewhere on the board
COL8: U2.27 (PD7); also elsewhere on the board
COL9: U2.26 (PD6); also elsewhere on the board
COL10: U2.25 (PD4); also elsewhere on the board
COL11: U2.22 (PD5); also elsewhere on the board
COL12: U2.21 (PD3); also elsewhere on the board
COL13: U2.20 (PD2); also elsewhere on the board
COL14: U2.19 (PD1); also elsewhere on the board
D+: J1.3, R1.2, U1.1 (IO1), USB1.6 (DP1), USB1.8 (DP2)
D-: J1.2, R2.2, U1.6 (IO4), USB1.5 (DN2), USB1.7 (DN1)
GND: C1.2, C2.2, C3.2, C4.2, C5.1, C6.2, C7.1, J1.4, J2.6 (GND), R3.1, R5.2, R6.2, SW1.1, U1.2 (VN), U2.5 (UGND), U2.15 (GND), U2.23 (GND), U2.35 (GND), U2.43 (GND), USB1.1 (GND), USB1.12 (GND), USB1.13 (SHIELD), Y1.2, Y1.4
MISO: J2.1 (MISO), U2.11 (PB3)
MOSI: J2.4 (MOSI), U2.10 (PB2)
unnamed: C6.1, U2.6 (UCAP)
unnamed: R3.2, U2.33 (~HWB/PE2)
unnamed: R5.1, USB1.4 (CC1)
unnamed: R6.1, USB1.10 (CC2)
ROW0: U2.1 (PE6); also elsewhere on the board
ROW1: U2.12 (PB7); also elsewhere on the board
ROW2: U2.36 (PF7); also elsewhere on the board
ROW3: U2.39 (PF4); also elsewhere on the board
ROW4: U2.38 (PF5); also elsewhere on the board
RST: J2.5 (~RST), R4.1, SW1.2, U2.13 (~RESET)
SCK: J2.3 (SCK), U2.9 (PB1)
VBUS: F1.2, F2.2, J1.1, U1.5 (VP), USB1.2 (VBUS), USB1.11 (VBUS)
XTAL1: C7.2, U2.17 (XTAL1), Y1.1
XTAL2: C5.2, U2.16 (XTAL2), Y1.3

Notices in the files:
keeb65/oled/oled_ssd1357.kicad_sch:
Copyright © 2022 HorrorTroll
MIT License
paws60/pcb/Hotswap/matrix.kicad_sch:
Copyright © 2020 kkatano
